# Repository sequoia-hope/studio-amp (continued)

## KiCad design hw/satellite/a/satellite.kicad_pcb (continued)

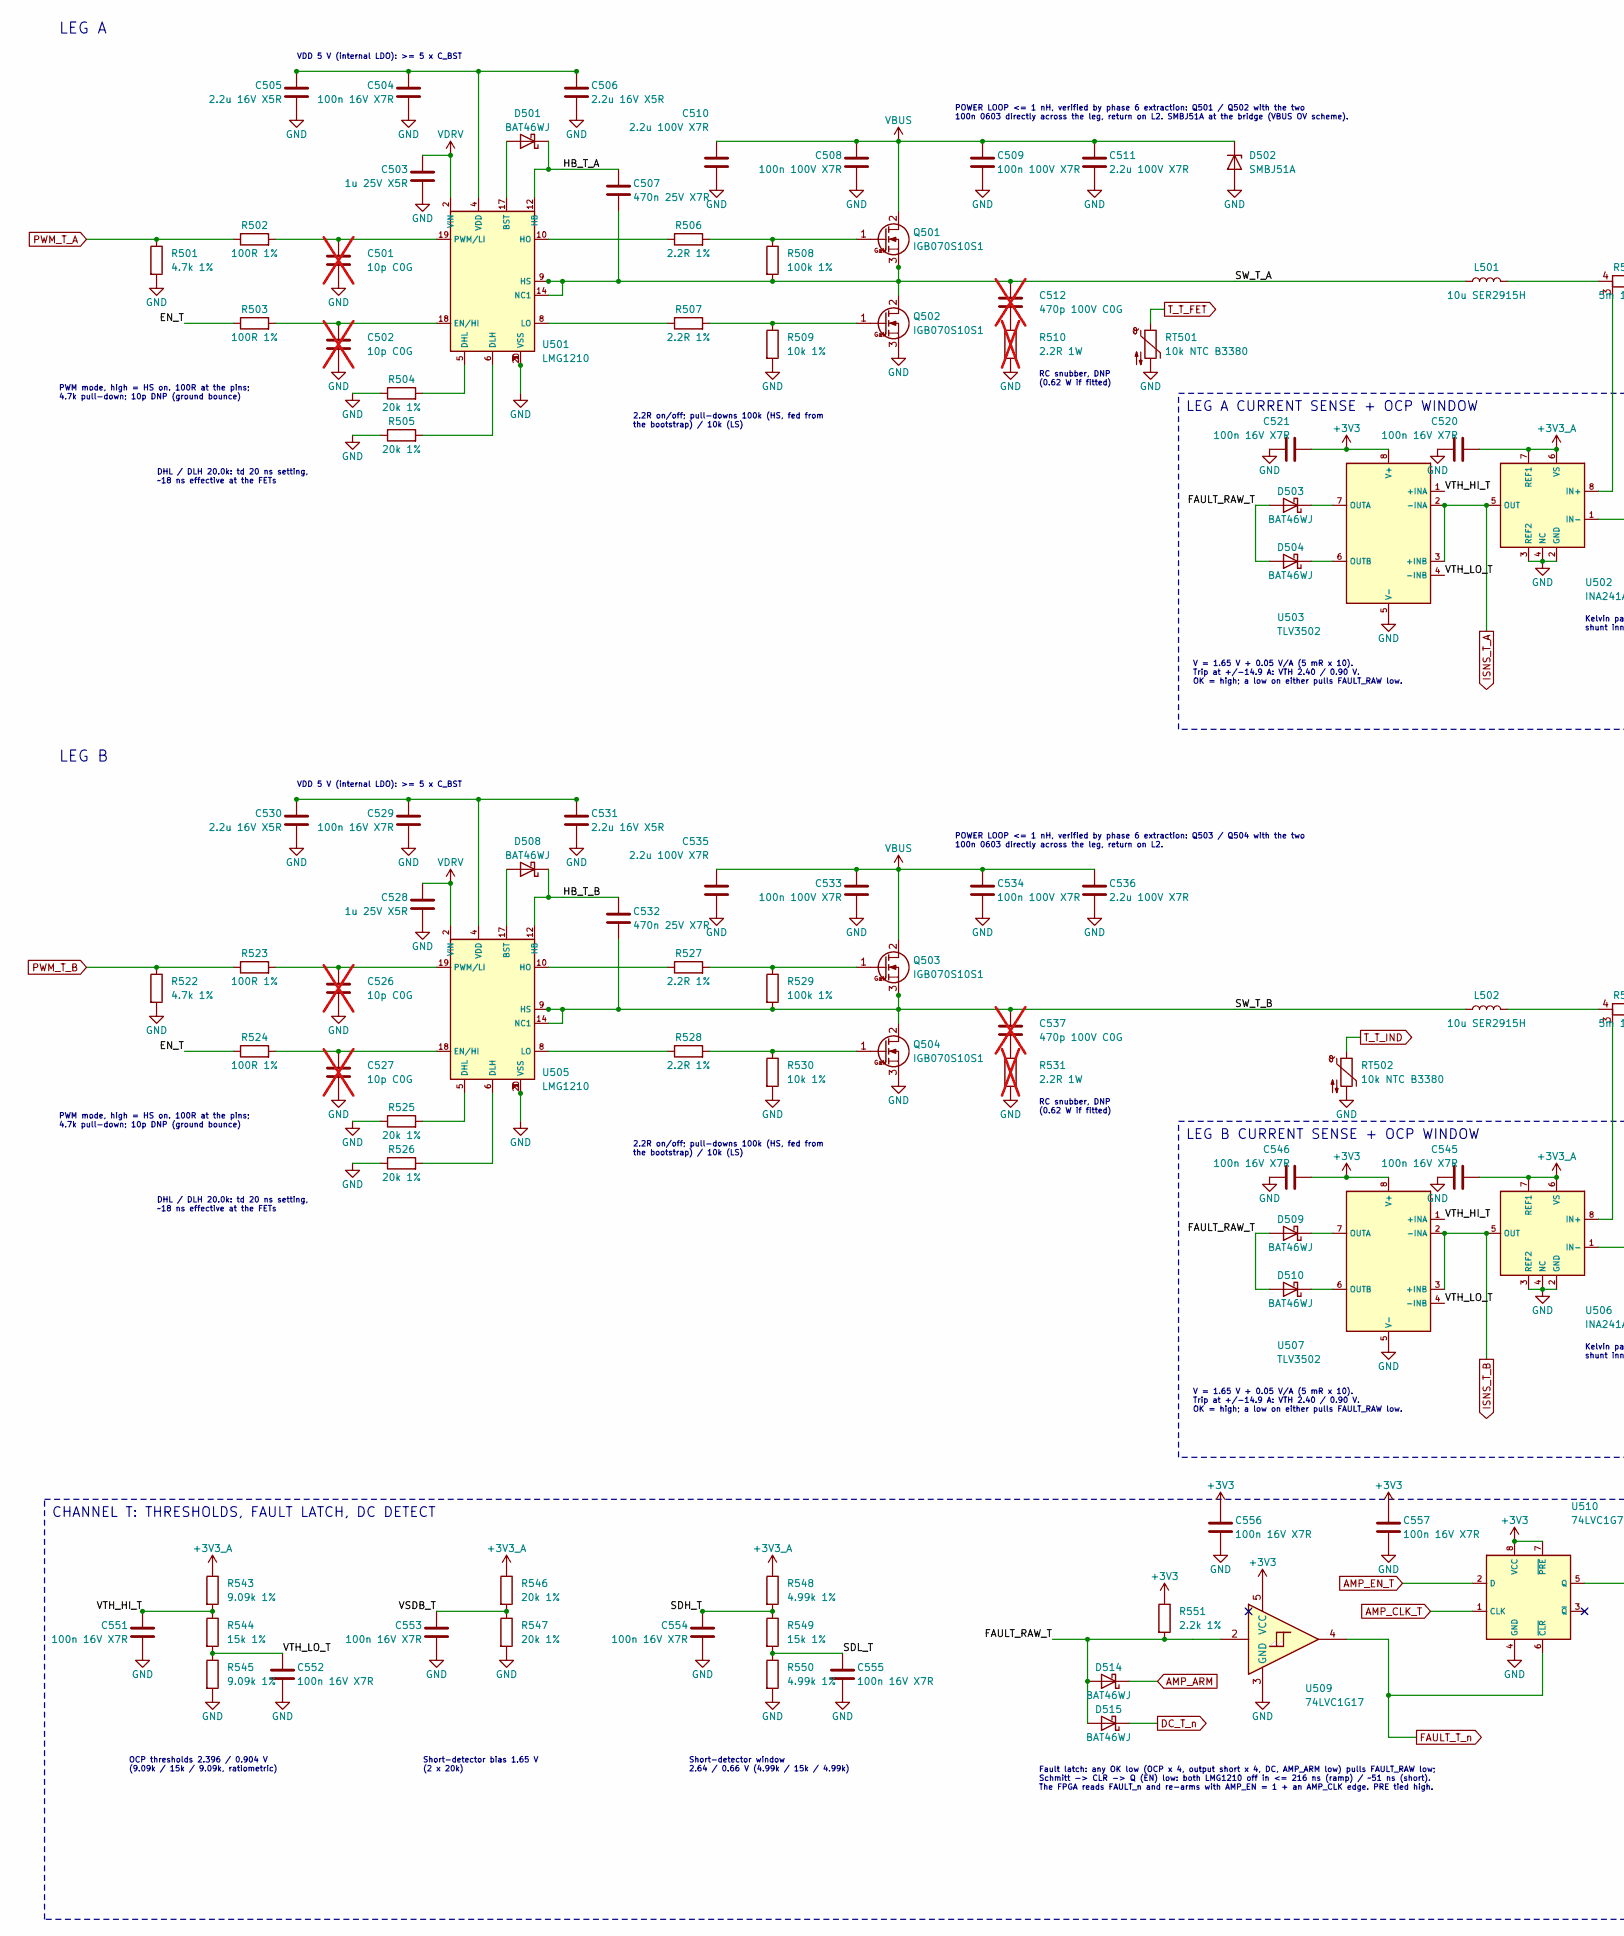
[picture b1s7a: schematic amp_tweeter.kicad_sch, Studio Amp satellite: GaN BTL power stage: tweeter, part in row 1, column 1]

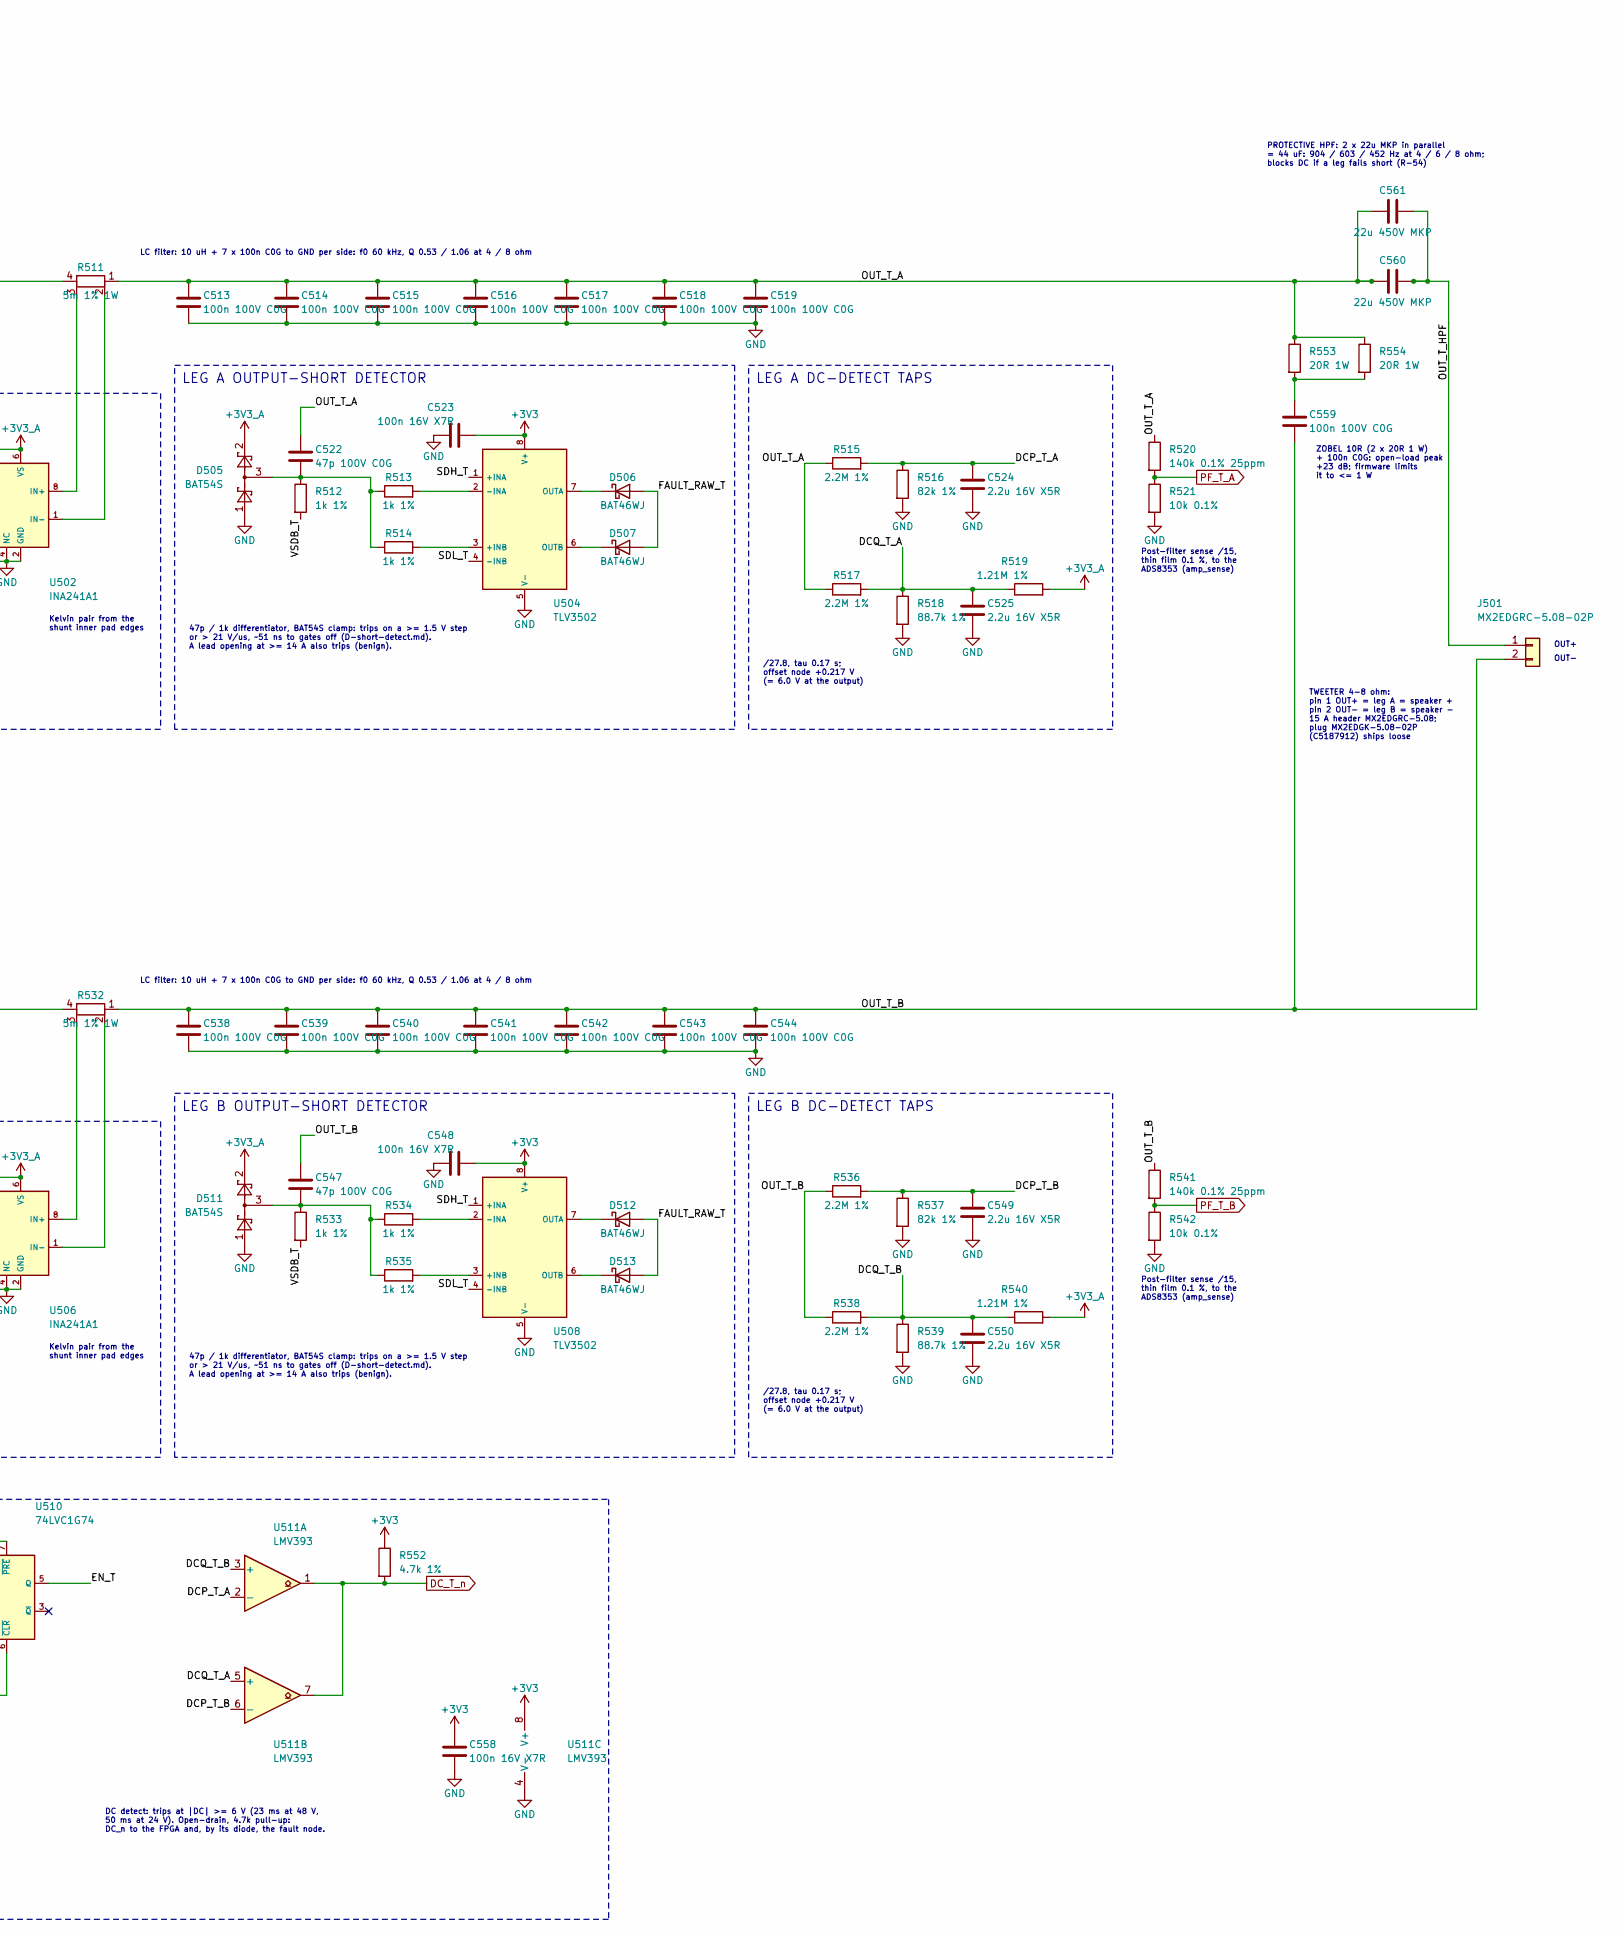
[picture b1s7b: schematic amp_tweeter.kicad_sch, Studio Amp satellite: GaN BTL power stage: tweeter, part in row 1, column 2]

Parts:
C501, C502, C526, C527: 10p C0G; C_0402_1005Metric; MPN 0402N100J500CT; LCSC C301961; not fitted
C503, C528: 1u 25V X5R; C_0603_1608Metric; MPN CL10A105KA8NNNC; LCSC C5673
C504, C520, C521, C523, C529, C545, C546, C548, C551, C552, C553, C554, C555, C556, C557, C558: 100n 16V X7R; C_0402_1005Metric; MPN CC0402KRX7R7BB104; LCSC C60474
C505, C506, C524, C525, C530, C531, C549, C550: 2.2u 16V X5R; C_0603_1608Metric; MPN CL10A225KO8NNNC; LCSC C23630
C507, C532: 470n 25V X7R; C_0603_1608Metric; MPN CL10B474KA8NNNC; LCSC C1623
C508, C509, C533, C534: 100n 100V X7R; C_0603_1608Metric; MPN HMK107B7104KAHT; LCSC C268011
C510, C511, C535, C536: 2.2u 100V X7R; C_1210_3225Metric; MPN HMK325B7225KN-T; LCSC C92775
C512, C537: 470p 100V C0G; C_0603_1608Metric; MPN CC0603JRNPO0BN471; LCSC C326973; not fitted
C513, C514, C515, C516, C517, C518, C519, C538, C539, C540, C541, C542, C543, C544, C559: 100n 100V C0G; C_1206_3216Metric; MPN GRM31C5C2A104JA01L; LCSC C405303
C522, C547: 47p 100V C0G; C_0603_1608Metric; MPN CC0603JRNPO0BN470; LCSC C327115
C560, C561: 22u 450V MKP; C_Rect_L31.5mm_W22.0mm_P27.50mm_B32774; MPN B32774D4226K; LCSC C531089
D501, D503, D504, D506, D507, D508, D509, D510, D512, D513, D514, D515: BAT46WJ; D_SOD-323F; MPN BAT46WJ,115; LCSC C114696
D502: SMBJ51A; D_SMB; MPN SMBJ51A; LCSC C1973217
D505, D511: BAT54S; SOT-23; MPN BAT54S,215; LCSC C47546
J501: MX2EDGRC-5.08-02P; MAX_MX2EDGRC-5.08-02P_1x02_P5.08mm_Horizontal; MPN MX2EDGRC-5.08-02P-GN01-Cu-A; LCSC C5188019
L501, L502: 10u SER2915H; Coilcraft_SER2915H; MPN SER2915H-103KL; LCSC C19276042
Q501, Q502, Q503, Q504: IGB070S10S1; IGB070S10S1_PG-TSON-4; MPN IGB070S10S1XTMA1; LCSC C44179579
R501, R522, R552: 4.7k 1%; R_0402_1005Metric; MPN 0402WGF4701TCE; LCSC C25900
R502, R503, R523, R524: 100R 1%; R_0402_1005Metric; MPN RC0402FR-07100RL; LCSC C106232
R504, R505, R525, R526, R546, R547: 20k 1%; R_0402_1005Metric; MPN 0402WGF2002TCE; LCSC C25765
R506, R507, R527, R528: 2.2R 1%; R_0402_1005Metric; MPN FRC0402F2R20TS; LCSC C2909330
R508, R529: 100k 1%; R_0402_1005Metric; MPN 0402WGF1003TCE; LCSC C25741
R509, R530: 10k 1%; R_0402_1005Metric; MPN 0402WGF1002TCE; LCSC C25744
R510, R531: 2.2R 1W; R_2512_6332Metric; MPN 25121WJ022JT4E; LCSC C25480; not fitted
R511, R532: 5m 1% 1W; R_2512_6332Metric_Kelvin_NetTie; MPN PA2512FKF070R005E; LCSC C723365
R512, R513, R514, R533, R534, R535: 1k 1%; R_0402_1005Metric; MPN 0402WGF1001TCE; LCSC C11702
R515, R517, R536, R538: 2.2M 1%; R_0603_1608Metric; MPN 0603WAF2204T5E; LCSC C22938
R516, R537: 82k 1%; R_0603_1608Metric; MPN 0603WAF8202T5E; LCSC C23254
R518, R539: 88.7k 1%; R_0603_1608Metric; MPN 0603WAF8872T5E; LCSC C23258
R519, R540: 1.21M 1%; R_0603_1608Metric; MPN 0603WAF1214T5E; LCSC C422998
R520, R541: 140k 0.1% 25ppm; R_0603_1608Metric; MPN RT0603BRD07140KL; LCSC C861125
R521, R542: 10k 0.1%; R_0603_1608Metric; MPN RT0603BRD0710KL; LCSC C95204
R543, R545: 9.09k 1%; R_0402_1005Metric; MPN 0402WGF9091TCE; LCSC C11549
R544, R549: 15k 1%; R_0402_1005Metric; MPN 0402WGF1502TCE; LCSC C25756
R548, R550: 4.99k 1%; R_0402_1005Metric; MPN 0402WGF4991TCE; LCSC C25903
R551: 2.2k 1%; R_0402_1005Metric; MPN 0402WGF2201TCE; LCSC C25879
R553, R554: 20R 1W; R_2512_6332Metric; MPN 25121WF200JT4E; LCSC C41950
RT501, RT502: 10k NTC B3380; R_0402_1005Metric; MPN NCP15XH103F03RC; LCSC C77131
U501, U505: LMG1210; Texas_RVR0019A_WQFN-19-2EP_4x3mm_P0.5mm; MPN LMG1210RVRR; LCSC C2677136
U502, U506: INA241A1; SOT-23-8; MPN INA241A1IDDFR; LCSC C19712054
U503, U504, U507, U508: TLV3502; SOT-23-8; MPN TLV3502AIDCNR; LCSC C48618
U509: 74LVC1G17; SOT-23-5; MPN SN74LVC1G17DBVR; LCSC C7836
U510: 74LVC1G74; VSSOP-8_2.3x2mm_P0.5mm; MPN SN74LVC1G74DCUR; LCSC C70285
U511: LMV393; SOIC-8_3.9x4.9mm_P1.27mm; MPN LMV393IDR; LCSC C7984

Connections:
+3V3_A: C520.2, C545.2, D505.2 (K), D511.2 (K), R519.2, R540.2, R543.1, R546.1, R548.1, U502.6 (VS), U502.7 (REF1), U506.6 (VS), U506.7 (REF1); also elsewhere on the board
/amp_tweeter/DCP_T_A: C524.1, R515.2, R516.1, U511.2 (-)
/amp_tweeter/DCP_T_B: C549.1, R536.2, R537.1, U511.6 (-)
/amp_tweeter/DCQ_T_A: C525.1, R517.2, R518.1, R519.1, U511.5 (+)
/amp_tweeter/DCQ_T_B: C550.1, R538.2, R539.1, R540.1, U511.3 (+)
/amp_tweeter/EN_T: R503.1, R524.1, U510.5 (Q)
/amp_tweeter/FAULT_RAW_T: D503.2 (A), D504.2 (A), D506.2 (A), D507.2 (A), D509.2 (A), D510.2 (A), D512.2 (A), D513.2 (A), D514.2 (A), D515.2 (A), R551.2, U509.2
/amp_tweeter/HB_T_A: C507.1, D501.1 (K), U501.12 (HB)
/amp_tweeter/HB_T_B: C532.1, D508.1 (K), U505.12 (HB)
/amp_tweeter/OUT_T_A: C513.1, C514.1, C515.1, C516.1, C517.1, C518.1, C519.1, C522.1, C560.1, C561.1, R511.1, R515.1, R517.1, R520.1, R553.1, R554.1
/amp_tweeter/OUT_T_B: C538.1, C539.1, C540.1, C541.1, C542.1, C543.1, C544.1, C547.1, C559.2, J501.2, R532.1, R536.1, R538.1, R541.1
/amp_tweeter/OUT_T_HPF: C560.2, C561.2, J501.1
/amp_tweeter/SDH_T: C554.1, R548.2, R549.1, U504.1 (+INA), U508.1 (+INA)
/amp_tweeter/SDL_T: C555.1, R549.2, R550.1, U504.4 (-INB), U508.4 (-INB)
/amp_tweeter/SW_T_A: C507.2, C512.1, L501.1, Q501.3 (S), Q501.4 (S), Q502.2 (D), R508.2, U501.9 (HS), U501.13 (HS), U501.14 (NC1), U501.16 (HS), U501.21 (HS)
/amp_tweeter/SW_T_B: C532.2, C537.1, L502.1, Q503.3 (S), Q503.4 (S), Q504.2 (D), R529.2, U505.9 (HS), U505.13 (HS), U505.14 (NC1), U505.16 (HS), U505.21 (HS)
/amp_tweeter/VSDB_T: C553.1, R512.2, R533.2, R546.2, R547.1
/amp_tweeter/VTH_HI_T: C551.1, R543.2, R544.1, U503.1 (+INA), U507.1 (+INA)
/amp_tweeter/VTH_LO_T: C552.1, R544.2, R545.1, U503.4 (-INB), U507.4 (-INB)
AMP_ARM: D514.1 (K); also elsewhere on the board
AMP_CLK_T: U510.1 (CLK); also elsewhere on the board
AMP_EN_T: U510.2 (D); also elsewhere on the board
DC_T_n: D515.1 (K), R552.2, U511.1, U511.7; also elsewhere on the board
FAULT_T_n: U509.4, U510.6 (~CLR); also elsewhere on the board
ISNS_T_A: U502.5 (OUT), U503.2 (-INA), U503.3 (+INB); also elsewhere on the board
ISNS_T_B: U506.5 (OUT), U507.2 (-INA), U507.3 (+INB); also elsewhere on the board
unnamed: C512.2, R510.1
unnamed: C537.2, R531.1
unnamed: C559.1, R553.2, R554.2
unnamed: D501.2 (A), U501.17 (BST)
unnamed: D503.1 (K), U503.7 (OUTA)
unnamed: D504.1 (K), U503.6 (OUTB)
unnamed: C522.2, D505.3 (COM), R512.1, R513.1, R514.1
unnamed: D506.1 (K), U504.7 (OUTA)
unnamed: D507.1 (K), U504.6 (OUTB)
unnamed: D508.2 (A), U505.17 (BST)
unnamed: D509.1 (K), U507.7 (OUTA)
unnamed: D510.1 (K), U507.6 (OUTB)
unnamed: C547.2, D511.3 (COM), R533.1, R534.1, R535.1
unnamed: D512.1 (K), U508.7 (OUTA)
unnamed: D513.1 (K), U508.6 (OUTB)
unnamed: L501.2, R511.4
unnamed: L502.2, R532.4
unnamed: Q501.1 (G), R506.2, R508.1
unnamed: Q502.1 (G), R507.2, R509.1
unnamed: Q503.1 (G), R527.2, R529.1
unnamed: Q504.1 (G), R528.2, R530.1
unnamed: R504.2, U501.5 (DHL)
unnamed: R505.2, U501.6 (DLH)
unnamed: C502.1, R503.2, U501.18 (EN/HI)
unnamed: R506.1, U501.10 (HO)
unnamed: R507.1, U501.8 (LO)
unnamed: C501.1, R502.2, U501.19 (PWM/LI)
unnamed: C504.1, C505.1, C506.1, U501.4 (VDD)
unnamed: R511.3, U502.8 (IN+)
unnamed: R511.2, U502.1 (IN-)
unnamed: R514.2, U504.3 (+INB)
unnamed: R513.2, U504.2 (-INA)
unnamed: R525.2, U505.5 (DHL)
unnamed: R526.2, U505.6 (DLH)
unnamed: C527.1, R524.2, U505.18 (EN/HI)
unnamed: R527.1, U505.10 (HO)
unnamed: R528.1, U505.8 (LO)
unnamed: C526.1, R523.2, U505.19 (PWM/LI)
unnamed: C529.1, C530.1, C531.1, U505.4 (VDD)
unnamed: R532.3, U506.8 (IN+)
unnamed: R532.2, U506.1 (IN-)
unnamed: R535.2, U508.3 (+INB)
unnamed: R534.2, U508.2 (-INA)
PF_T_A: R520.2, R521.1; also elsewhere on the board
PF_T_B: R541.2, R542.1; also elsewhere on the board
PWM_T_A: R501.1, R502.1; also elsewhere on the board
PWM_T_B: R522.1, R523.1; also elsewhere on the board
T_T_FET: RT501.1; also elsewhere on the board
T_T_IND: RT502.1; also elsewhere on the board

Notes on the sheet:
LEG A
PWM mode, high = HS on. 100R at the pins; 4.7k pull-down; 10p DNP (ground bounce)
DHL / DLH 20.0k: td 20 ns setting, ~18 ns effective at the FETs
VDD 5 V (internal LDO): >= 5 x C_BST
2.2R on/off; pull-downs 100k (HS, fed from the bootstrap) / 10k (LS)
POWER LOOP <= 1 nH, verified by phase 6 extraction: Q501 / Q502 with the two 100n 0603 directly across the leg, return on L2. SMBJ51A at the bridge (VBUS OV scheme).
RC snubber, DNP (0.62 W if fitted)
LC filter: 10 uH + 7 x 100n C0G to GND per side: f0 60 kHz, Q 0.53 / 1.06 at 4 / 8 ohm
Kelvin pair from the shunt inner pad edges
LEG A CURRENT SENSE + OCP WINDOW
V = 1.65 V + 0.05 V/A (5 mR x 10). Trip at +/-14.9 A: VTH 2.40 / 0.90 V. OK = high; a low on either pulls FAULT_RAW low.
LEG A OUTPUT-SHORT DETECTOR
47p / 1k differentiator, BAT54S clamp: trips on a >= 1.5 V step or > 21 V/us, ~51 ns to gates off (D-short-detect.md). A lead opening at >= 14 A also trips (benign).
LEG A DC-DETECT TAPS
/27.8, tau 0.17 s; offset node +0.217 V (= 6.0 V at the output)
Post-filter sense /15, thin film 0.1 %, to the ADS8353 (amp_sense)
LEG B
POWER LOOP <= 1 nH, verified by phase 6 extraction: Q503 / Q504 with the two 100n 0603 directly across the leg, return on L2.
LEG B CURRENT SENSE + OCP WINDOW
LEG B OUTPUT-SHORT DETECTOR
LEG B DC-DETECT TAPS
CHANNEL T: THRESHOLDS, FAULT LATCH, DC DETECT
OCP thresholds 2.396 / 0.904 V (9.09k / 15k / 9.09k, ratiometric)
Short-detector bias 1.65 V (2 x 20k)
Short-detector window 2.64 / 0.66 V (4.99k / 15k / 4.99k)
Fault latch: any OK low (OCP x 4, output short x 4, DC, AMP_ARM low) pulls FAULT_RAW low; Schmitt -> CLR -> Q (EN) low: both LMG1210 off in <= 216 ns (ramp) / ~51 ns (short). The FPGA reads FAULT_n and re-arms with AMP_EN = 1 + an AMP_CLK edge. PRE tied high.
DC detect: trips at |DC| >= 6 V (23 ms at 48 V, 50 ms at 24 V). Open-drain, 4.7k pull-up: DC_n to the FPGA and, by its diode, the fault node.
ZOBEL 10R (2 x 20R 1 W) + 100n C0G: open-load peak +23 dB; firmware limits it to <= 1 W
PROTECTIVE HPF: 2 x 22u MKP in parallel = 44 uF: 904 / 603 / 452 Hz at 4 / 6 / 8 ohm; blocks DC if a leg fails short (R-54)
OUT+
OUT-
TWEETER 4-8 ohm: pin 1 OUT+ = leg A = speaker + pin 2 OUT- = leg B = speaker - 15 A header MX2EDGRC-5.08; plug MX2EDGK-5.08-02P (C5187912) ships loose

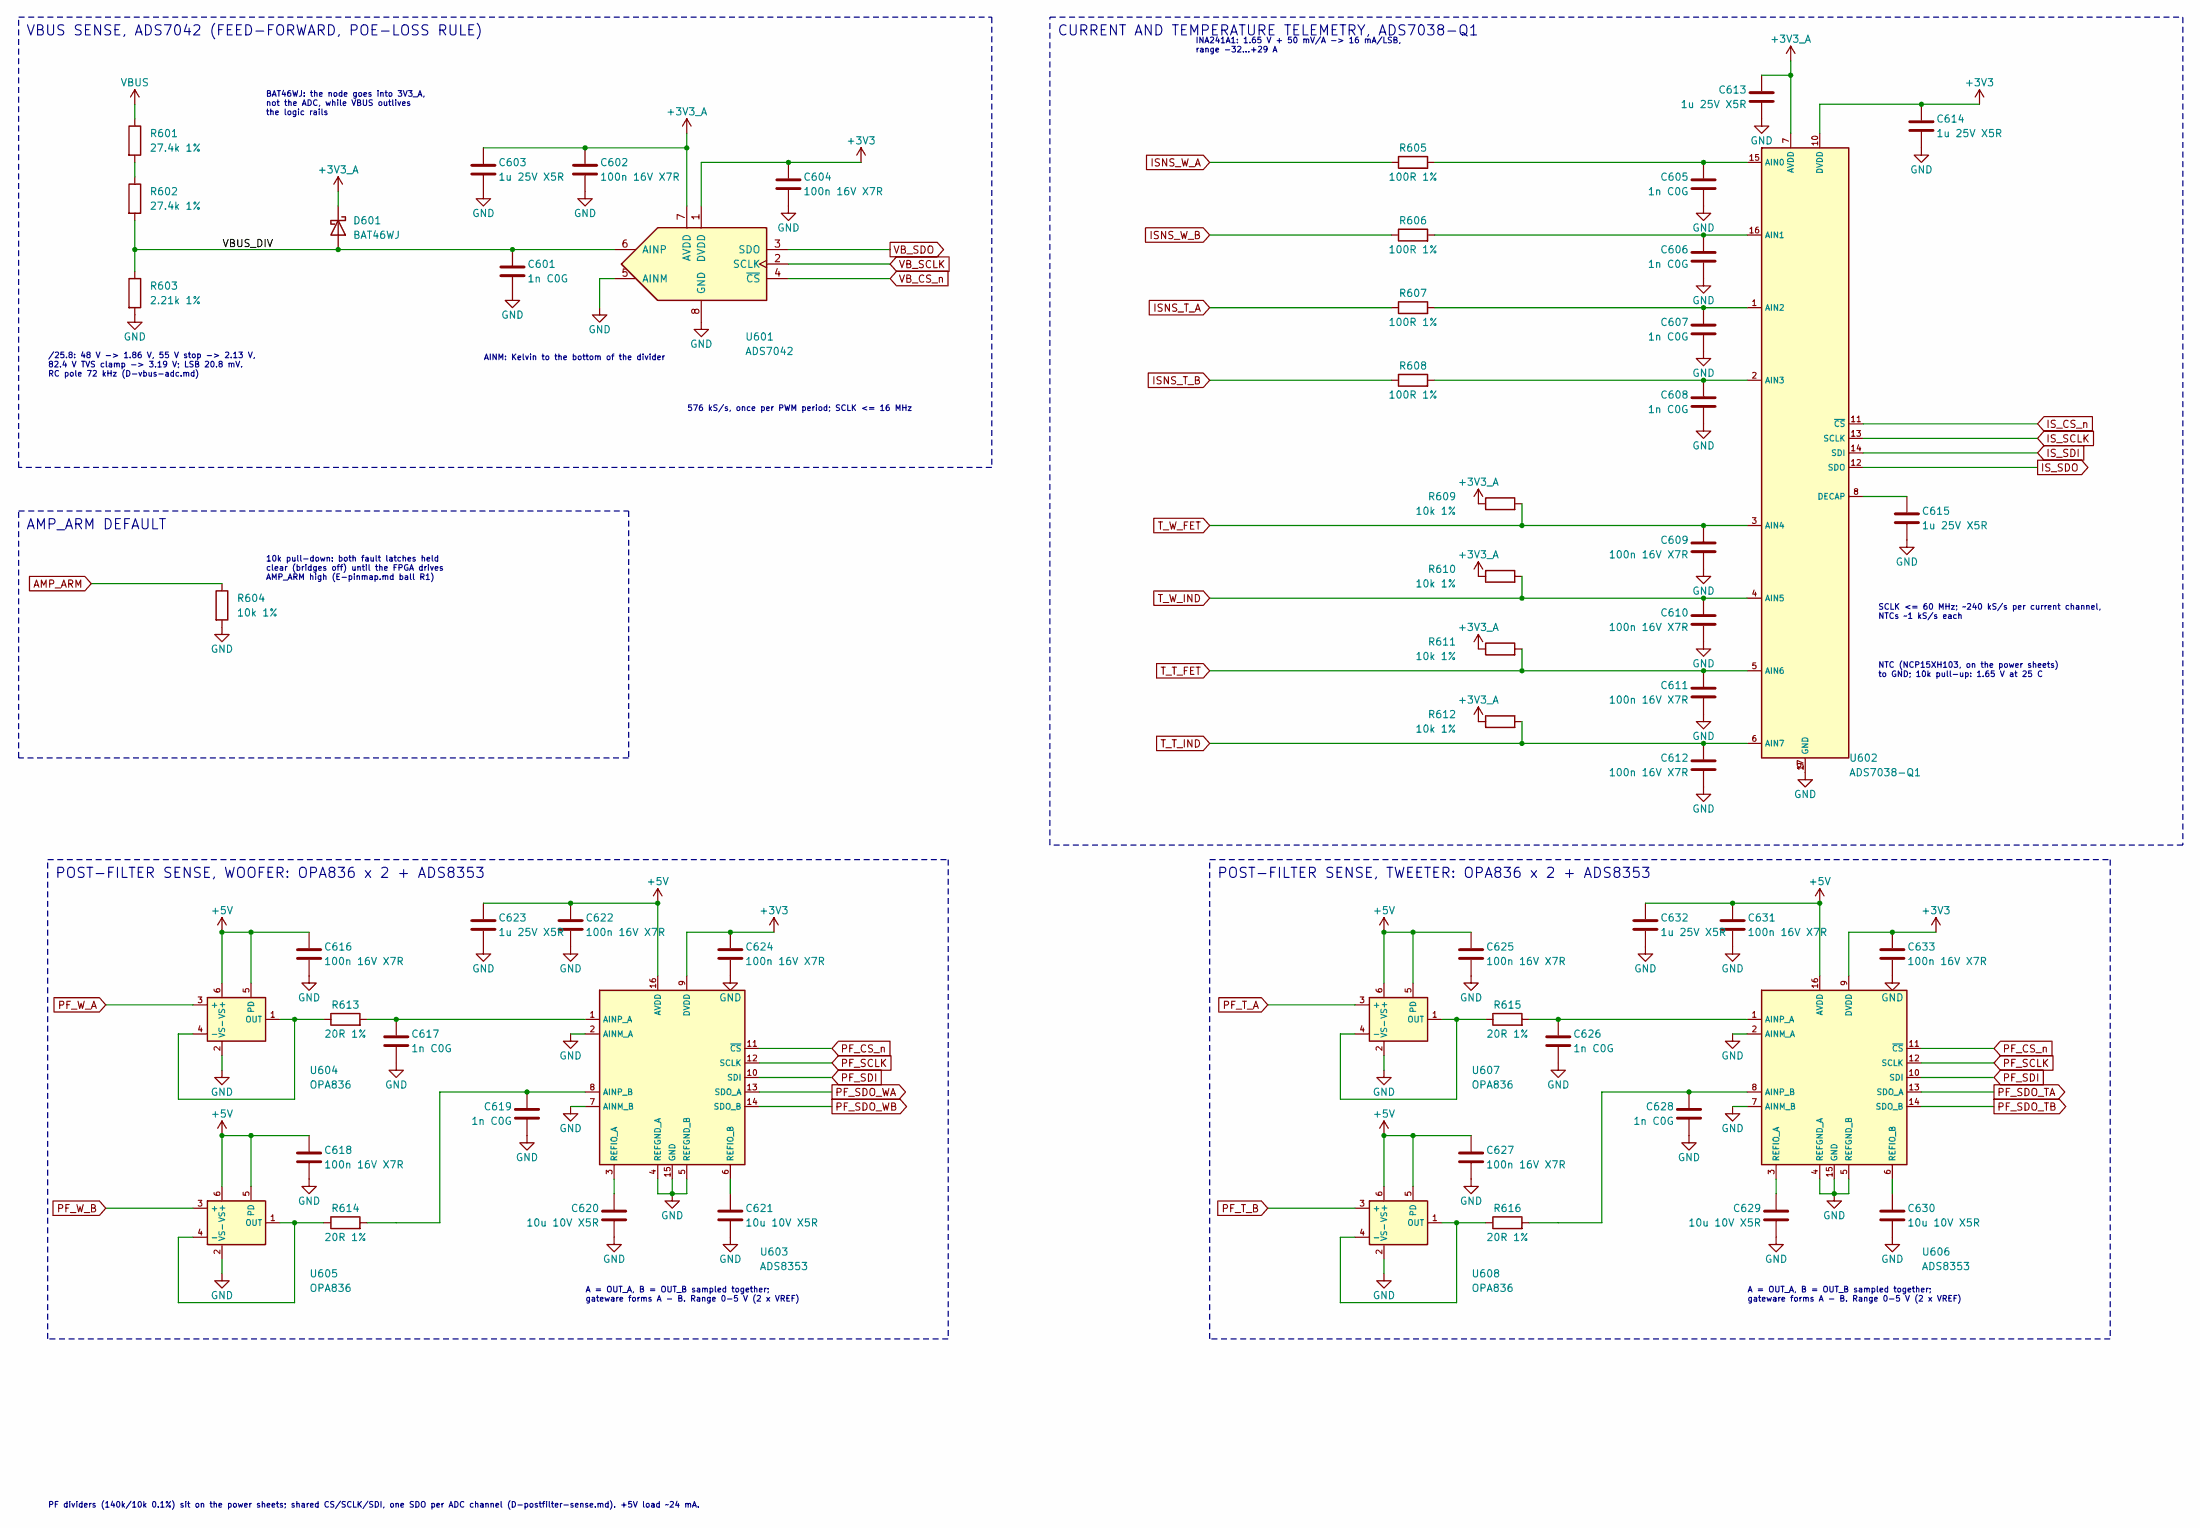
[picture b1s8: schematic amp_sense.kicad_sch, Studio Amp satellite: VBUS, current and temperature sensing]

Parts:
C601, C605, C606, C607, C608, C617, C619, C626, C628: 1n C0G; C_0402_1005Metric; MPN 0402N102J500CT; LCSC C237166
C602, C604, C609, C610, C611, C612, C616, C618, C622, C624, C625, C627, C631, C633: 100n 16V X7R; C_0402_1005Metric; MPN CC0402KRX7R7BB104; LCSC C60474
C603, C613, C614, C615, C623, C632: 1u 25V X5R; C_0603_1608Metric; MPN CL10A105KA8NNNC; LCSC C5673
C620, C621, C629, C630: 10u 10V X5R; C_0603_1608Metric; MPN CL10A106KP8NNNC; LCSC C19702
D601: BAT46WJ; D_SOD-323F; MPN BAT46WJ,115; LCSC C114696
R601, R602: 27.4k 1%; R_0805_2012Metric; MPN FRC0805F2742TS; LCSC C2930188
R603: 2.21k 1%; R_0603_1608Metric; MPN FRC0603F2211TS; LCSC C2933171
R604, R609, R610, R611, R612: 10k 1%; R_0402_1005Metric; MPN 0402WGF1002TCE; LCSC C25744
R605, R606, R607, R608: 100R 1%; R_0402_1005Metric; MPN RC0402FR-07100RL; LCSC C106232
R613, R614, R615, R616: 20R 1%; R_0402_1005Metric; MPN RC0402FR-0720RL; LCSC C138031
U601: ADS7042; VSSOP-8_2.3x2mm_P0.5mm; MPN ADS7042IDCUR; LCSC C701641
U602: ADS7038-Q1; WQFN-16-1EP_3x3mm_P0.5mm_EP1.68x1.68mm; MPN ADS7038QRTERQ1; LCSC C2876384
U603, U606: ADS8353; TSSOP-16_4.4x5mm_P0.65mm; MPN ADS8353IPWR; LCSC C701691
U604, U605, U607, U608: OPA836; SOT-23-6; MPN OPA836IDBVR; LCSC C111589

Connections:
+3V3_A: C602.1, C603.1, C613.1, D601.1 (K), R609.1, R610.1, R611.1, R612.1, U601.7 (AVDD), U602.7 (AVDD); also elsewhere on the board
+5V: C616.1, C618.1, C622.1, C623.1, C625.1, C627.1, C631.1, C632.1, U603.16 (AVDD), U604.5 (PD), U604.6 (VS+), U605.5 (PD), U605.6 (VS+), U606.16 (AVDD), U607.5 (PD), U607.6 (VS+), U608.5 (PD), U608.6 (VS+); also elsewhere on the board
/amp_sense/VBUS_DIV: C601.1, D601.2 (A), R602.2, R603.1, U601.6 (AINP)
AMP_ARM: R604.1; also elsewhere on the board
ISNS_T_A: R607.1; also elsewhere on the board
ISNS_T_B: R608.1; also elsewhere on the board
ISNS_W_A: R605.1; also elsewhere on the board
ISNS_W_B: R606.1; also elsewhere on the board
IS_CS_n: U602.11 (~CS); also elsewhere on the board
IS_SCLK: U602.13 (SCLK); also elsewhere on the board
IS_SDI: U602.14 (SDI); also elsewhere on the board
IS_SDO: U602.12 (SDO); also elsewhere on the board
unnamed: R601.2, R602.1
unnamed: C605.1, R605.2, U602.15 (AIN0)
unnamed: C606.1, R606.2, U602.16 (AIN1)
unnamed: C607.1, R607.2, U602.1 (AIN2)
unnamed: C608.1, R608.2, U602.2 (AIN3)
unnamed: C615.1, U602.8 (DECAP)
unnamed: C617.1, R613.2, U603.1 (AINP_A)
unnamed: C619.1, R614.2, U603.8 (AINP_B)
unnamed: C620.1, U603.3 (REFIO_A)
unnamed: C621.1, U603.6 (REFIO_B)
unnamed: R613.1, U604.1 (OUT), U604.4 (-)
unnamed: R614.1, U605.1 (OUT), U605.4 (-)
unnamed: C626.1, R615.2, U606.1 (AINP_A)
unnamed: C628.1, R616.2, U606.8 (AINP_B)
unnamed: C629.1, U606.3 (REFIO_A)
unnamed: C630.1, U606.6 (REFIO_B)
unnamed: R615.1, U607.1 (OUT), U607.4 (-)
unnamed: R616.1, U608.1 (OUT), U608.4 (-)
PF_CS_n: U603.11 (~CS), U606.11 (~CS); also elsewhere on the board
PF_SCLK: U603.12 (SCLK), U606.12 (SCLK); also elsewhere on the board
PF_SDI: U603.10 (SDI), U606.10 (SDI); also elsewhere on the board
PF_SDO_TA: U606.13 (SDO_A); also elsewhere on the board
PF_SDO_TB: U606.14 (SDO_B); also elsewhere on the board
PF_SDO_WA: U603.13 (SDO_A); also elsewhere on the board
PF_SDO_WB: U603.14 (SDO_B); also elsewhere on the board
PF_T_A: U607.3 (+); also elsewhere on the board
PF_T_B: U608.3 (+); also elsewhere on the board
PF_W_A: U604.3 (+); also elsewhere on the board
PF_W_B: U605.3 (+); also elsewhere on the board
T_T_FET: C611.1, R611.2, U602.5 (AIN6); also elsewhere on the board
T_T_IND: C612.1, R612.2, U602.6 (AIN7); also elsewhere on the board
T_W_FET: C609.1, R609.2, U602.3 (AIN4); also elsewhere on the board
T_W_IND: C610.1, R610.2, U602.4 (AIN5); also elsewhere on the board
VB_CS_n: U601.4 (~CS); also elsewhere on the board
VB_SCLK: U601.2 (SCLK); also elsewhere on the board
VB_SDO: U601.3 (SDO); also elsewhere on the board

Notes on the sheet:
VBUS SENSE, ADS7042 (FEED-FORWARD, POE-LOSS RULE)
/25.8: 48 V -> 1.86 V, 55 V stop -> 2.13 V, 82.4 V TVS clamp -> 3.19 V; LSB 20.8 mV. RC pole 72 kHz (D-vbus-adc.md)
BAT46WJ: the node goes into 3V3_A, not the ADC, while VBUS outlives the logic rails
AINM: Kelvin to the bottom of the divider
576 kS/s, once per PWM period; SCLK <= 16 MHz
AMP_ARM DEFAULT
10k pull-down: both fault latches held clear (bridges off) until the FPGA drives AMP_ARM high (E-pinmap.md ball R1)
CURRENT AND TEMPERATURE TELEMETRY, ADS7038-Q1
INA241A1: 1.65 V + 50 mV/A -> 16 mA/LSB, range -32...+29 A
NTC (NCP15XH103, on the power sheets) to GND; 10k pull-up: 1.65 V at 25 C
SCLK <= 60 MHz; ~240 kS/s per current channel, NTCs ~1 kS/s each
POST-FILTER SENSE, WOOFER: OPA836 x 2 + ADS8353
A = OUT_A, B = OUT_B sampled together; gateware forms A - B. Range 0-5 V (2 x VREF)
POST-FILTER SENSE, TWEETER: OPA836 x 2 + ADS8353
PF dividers (140k/10k 0.1%) sit on the power sheets; shared CS/SCLK/SDI, one SDO per ADC channel (D-postfilter-sense.md). +5V load ~24 mA.

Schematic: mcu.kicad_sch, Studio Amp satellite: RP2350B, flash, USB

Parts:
C701, C707, C718: 4u7; C_0402_1005Metric; MPN CL05A475MP5NRNC; LCSC C23733
C702, C703: 4u7; C_0402_1005Metric_RPi_SmallPads; MPN CL05A475MP5NRNC; LCSC C23733
C704, C705, C706, C709, C710, C711, C712, C713, C714, C715, C716, C717, C719, C720, C723: 100n; C_0402_1005Metric; MPN CL05B104KO5NNNC; LCSC C1525
C708: 10u; C_0603_1608Metric; MPN CL10A106KP8NNNC; LCSC C19702
C721, C722: 15p; C_0402_1005Metric; MPN 0402CG150J500NT; LCSC C1548
L701: 3.3u; L_Abracon_AOTA-B201610S3R3_pol; MPN AOTA-B201610S3R3-101-T; LCSC C42411119
R701, R703: 33R; R_0402_1005Metric; MPN 0402WGF330JTCE; LCSC C25105
R702: 10R; R_0402_1005Metric; MPN 0402WGF100JTCE; LCSC C25077
R704, R707: 1k; R_0402_1005Metric; MPN 0402WGF1001TCE; LCSC C11702
R705: 10k; R_0402_1005Metric; MPN 0402WGF1002TCE; LCSC C25744
R706: 10k; R_0402_1005Metric; MPN 0402WGF1002TCE; LCSC C25744; not fitted
R708, R709: 27R; R_0402_1005Metric; MPN 0402WGF270JTCE; LCSC C25100
SW701: RUN; SW_Push_1P1T_XKB_TS-1187A; MPN TS-1187A-B-A-B; LCSC C318884
SW702: BOOTSEL; SW_Push_1P1T_XKB_TS-1187A; MPN TS-1187A-B-A-B; LCSC C318884
U701: RP2350B; QFN-80-1EP_10x10mm_P0.4mm_EP3.4x3.4mm; MPN RP2350B; LCSC C42415655
U702: W25Q128JVSIQ; SOIC-8_5.3x5.3mm_P1.27mm; MPN W25Q128JVSIQ; LCSC C97521
Y701: 12MHz; Crystal_SMD_3225-4Pin_3.2x2.5mm; MPN ABM8-272-T3; LCSC C20625731

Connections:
ENC1_A: U701.3 (GPIO6); also elsewhere on the board
ENC1_B: U701.4 (GPIO7); also elsewhere on the board
ENC2_A: U701.20 (GPIO20); also elsewhere on the board
ENC2_B: U701.21 (GPIO21); also elsewhere on the board
FPGA_CCLK: R703.2; also elsewhere on the board
FPGA_DONE: U701.36 (GPIO28); also elsewhere on the board
FPGA_INITN: U701.23 (GPIO23); also elsewhere on the board
FPGA_MISO: U701.25 (GPIO24); also elsewhere on the board
FPGA_MOSI: U701.28 (GPIO27); also elsewhere on the board
FPGA_PROGRAMN: U701.22 (GPIO22); also elsewhere on the board
FPGA_SN: U701.26 (GPIO25); also elsewhere on the board
I2C1_SCL: U701.80 (GPIO3); also elsewhere on the board
I2C1_SDA: U701.79 (GPIO2); also elsewhere on the board
IBUS_SENSE: C720.1, U701.55 (GPIO44/ADC4); also elsewhere on the board
ILIM_SEL0: U701.43 (GPIO34); also elsewhere on the board
ILIM_SEL1: U701.44 (GPIO35); also elsewhere on the board
KNOB1: U701.49 (GPIO40/ADC0); also elsewhere on the board
KNOB2: U701.52 (GPIO41/ADC1); also elsewhere on the board
KNOB3: U701.53 (GPIO42/ADC2); also elsewhere on the board
KNOB4: U701.54 (GPIO43/ADC3); also elsewhere on the board
LED_CLK: U701.2 (GPIO5); also elsewhere on the board
LED_DATA: U701.1 (GPIO4); also elsewhere on the board
LINK_CLK: U701.16 (GPIO16); also elsewhere on the board
LINK_D0: U701.6 (GPIO8); also elsewhere on the board
LINK_D1: U701.7 (GPIO9); also elsewhere on the board
LINK_D2: U701.8 (GPIO10); also elsewhere on the board
LINK_D3: U701.9 (GPIO11); also elsewhere on the board
LINK_D4: U701.11 (GPIO12); also elsewhere on the board
LINK_D5: U701.12 (GPIO13); also elsewhere on the board
LINK_D6: U701.13 (GPIO14); also elsewhere on the board
LINK_D7: U701.14 (GPIO15); also elsewhere on the board
LINK_DIR: U701.17 (GPIO17); also elsewhere on the board
LINK_IRQ: U701.19 (GPIO19); also elsewhere on the board
LINK_STB: U701.18 (GPIO18); also elsewhere on the board
unnamed: C722.1, R704.1, Y701.1
unnamed: R707.1, SW702.1
unnamed: R703.1, U701.27 (GPIO26)
unnamed: U701.71 (QSPI_SCLK), U702.6 (CLK)
unnamed: U701.72 (QSPI_SD0), U702.5 (DI/IO_{0})
unnamed: U701.74 (QSPI_SD1), U702.2 (DO/IO_{1})
unnamed: U701.73 (QSPI_SD2), U702.3 (~WP/IO_{2})
unnamed: U701.70 (QSPI_SD3), U702.7 (~HOLD/~RESET/IO_{3})
unnamed: R708.1, U701.66 (USB_DM)
unnamed: R709.1, U701.67 (USB_DP)
unnamed: C721.1, U701.30 (XIN), Y701.3
unnamed: R704.2, U701.31 (XOUT)
unnamed: R706.2, R707.2, U701.75 (~QSPI_SS), U702.1 (~CS)
unnamed: L701.2, U701.63 (VREG_LX)
RUN: R705.2, SW701.2, U701.35 (RUN); also elsewhere on the board
SWCLK: U701.33 (SWCLK); also elsewhere on the board
SWDIO: U701.34 (SWDIO); also elsewhere on the board
UART0_RX: U701.78 (GPIO1); also elsewhere on the board
UART0_TX: U701.77 (GPIO0); also elsewhere on the board
USB_DM: R708.2; also elsewhere on the board
USB_DP: R709.2; also elsewhere on the board
VDRV_EN: U701.45 (GPIO36); also elsewhere on the board
VDRV_PG: U701.42 (GPIO33); also elsewhere on the board

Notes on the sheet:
VREG_PGND (62) joins GND at ONE point, two adjacent vias (RP2350 6.3.8.1).
Core regulator, RP2350 6.3.8 / Minimal board: CIN, L and COUT on the chip's side; copy the reference corner (chips/rp2350.md). L: AOTA-B201610S3R3 3.3u, dot to DVDD_RP, reference rotation (orientation changes Vout). DVDD_RP is the RP2350's own 1.1 V (internal regulator); it is not the FPGA's +1V1.
PIO link to the ECP5 (E-link.md): 8-bit, 37.5 MHz, 22R series at each driver is in the FPGA design rule; LINK_* tri-stated while the FPGA is configured. ENC_*: encoder header on the io sheet (block G pulls).
SSPI configuration (SPI1): FPGA_CCLK 33R at the RP2350, pad set to 8 mA (1k pull-up at the FPGA). Reads <= 18.75 MHz, bitstream writes 37.5 MHz. IBUS_SENSE: 100n at the pin (B's 67k source, 24 Hz). ILIM_SEL0/1, VDRV_EN: reset Hi-Z, pulled down at blocks B and C (safe state).
ABM8-272-T3 12 MHz with 15p + 15p and 1k at XOUT: Raspberry Pi's tuned network (guide 4); traces < 5 mm.
Boot flash W25Q128JVSIQ (16 MB). QSPI <= 15 mm, nothing else between flash and RP2350. QSPI_SS: 10k pull-up footprint DNP (reference R1); 1k to BOOTSEL (reference R6).
USB 2.0 FS: 27R at the chip (guide 5.1); connector and ESD on the io sheet.
